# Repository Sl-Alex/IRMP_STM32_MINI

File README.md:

# IRMP Mini Board

This repository contains both PCB and case for IRMP project.
IRMP stands for "**I**nfra**R**ed **M**ulti**P**rotocol decoder".
This board is for STM32 port, which is developed by [Jörg Riechardt][1] and slightly modified (mostly pin assignments) by me.

## Assembly

![Assembly preview][pic_assembly]

## Schematic

![Schematic][pic_schematic]

## Components

As you see, there are not too much components. In fact, the board can be assembled in about half an hour or less, depending on your soldering skills. Please be aware that the smallest components are in size 0402, which is still perfectly solderable, although may require some practice and patience. This is done intentionally to keep the size small.

Here is a list of components to order:

|Reference        | Quantity | Value           | Footprint    | Remark                                                                                  |
| --------------- | -------- | --------------- | ------------ | --------------------------------------------------------------------------------------- |
| C1              | 1        | 100.0µ          | Case B       | Tantalum capacitor                                                                      |
| C2 C5           | 2        | 15p             | 0402         |                                                                                         |
| C3 C6           | 2        | 1.0u            | 0603         |                                                                                         |
| C4 C7 C8 C9 C10 | 5        | 0.1u            | 0402         |                                                                                         |
| D1              | 1        | GREEN           | 0603         |                                                                                         |
| D2              | 1        | RED             | 0603         |                                                                                         |
| R1 R2           | 2        | 20              | 0402         |                                                                                         |
| R3              | 1        | 4k7             | 0402         |                                                                                         |
| R4              | 1        | 100             | 0402         |                                                                                         |
| R5 R6           | 2        | 1k              | 0402         |                                                                                         |
| U1              | 1        | TSOP77338       | Heimdall     | Vishay Heimdall package                                                                 |
| U2              | 1        | MIC5504-3.3YM5  | SOT-23-5     |                                                                                         |
| U3              | 1        | STM32F103T8U6   | VFQFPN-36    |                                                                                         |
| X1              | 1        | 10118192-0001LF | USB2_MICRO_B | Most common USB micro B package. 10118192-0001LF from Amphenol ICC (FCI) fits perfectly |
| XC1             | 1        | 8MHz            | 3225         | 4 pin passive crystal in SMD 3225 package                                               |

## HowTo

- Order all components or make sure they are available
- Order the board. Gerbers are [here][2]
- Solder the board. I'd suggest soldering USB connector and power supply part first, checking if it works and then soldering the rest
- Download DFU bootloader [here][3]
- Flash the DFU bootloader using your favourite SWD adapter. Pin assignments are in the [assembly section](#assembly).
- Connect the board. It will be recognized as "STM32 Bootloader"
- Take the fw [here][4] (the most recent ```*IrmpMini_BL*.bin```)
- Run ```dfu-util -w -D <path_to_the_fw>```. DFU utility can be taken [here][5]
- Wait until the new FW is downloaded
- Reconnect the board

[pic_assembly]: images/pcb.png
[pic_schematic]: images/schematic.png

[1]: https://github.com/j1rie
[2]: https://github.com/Sl-Alex/IRMP_STM32_MINI/tree/main/plots
[3]: https://github.com/Sl-Alex/STM32F103-bootloader/raw/master/binaries/boot.IrmpMini.bin
[4]: https://github.com/Sl-Alex/IRMP_STM32/tree/master/binaries/firmware_for_bootloader
[5]: https://github.com/Sl-Alex/IRMP_STM32/tree/master/binaries/bootloader

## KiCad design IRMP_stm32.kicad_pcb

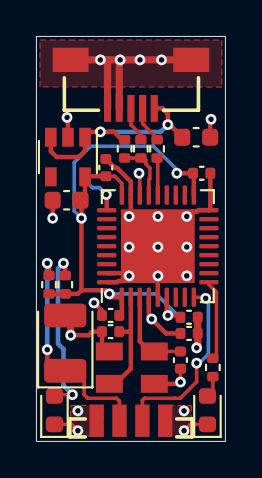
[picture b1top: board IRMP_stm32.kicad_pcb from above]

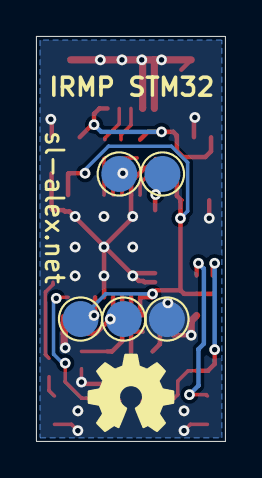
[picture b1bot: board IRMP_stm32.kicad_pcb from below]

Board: 2 copper layers, 10.5 x 22.5 mm, 29 parts (6 on the bottom side), 17 nets.

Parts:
C1: 100.0; CP_EIA-3528-21_Kemet-B
C2, C5: 15p; C_0402_1005Metric
C3, C6: 1.0; C_0603_1608Metric
C4, C7, C8, C9, C10: 0.1; C_0402_1005Metric
D1: GREEN; LED_0603_1608Metric
D2: RED; LED_0603_1608Metric
LG?1: LOGO; OSHW
R1, R2: 20; R_0402_1005Metric
R3: 4k7; R_0402_1005Metric
R4: 100; R_0402_1005Metric
R5, R6: 1k; R_0402_1005Metric
TP1: NRST; TestPoint_Pad_D2.0mm
TP2: 3V3; TestPoint_Pad_D2.0mm
TP3: GND; TestPoint_Pad_D2.0mm
TP4: SWDIO; TestPoint_Pad_D2.0mm
TP5: SWCLK; TestPoint_Pad_D2.0mm
U1: TSOP77338; Vishay_Heimdall
U2: MIC5504-3.3YM5; SOT-23-5
U3: STM32F103T8U6; QFN-36-1EP_6x6mm_P0.5mm_EP4.1x4.1mm
X1: 10118192-0001LF; USB2_MICRO_B_F1
XC1: 8MHz; SMD_3225

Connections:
+3V3: C6.2, C7.2, C8.2, C9.2, C10.2, R4.2, R6.2, TP2.1, U2.5, U3.1, U3.6, U3.19, U3.27
+5V: C3.2, R3.2, U2.1, U2.3, X1.1
/IR_PIN: U1.3, U3.9
/IR_PWR: C1.1, R4.1, U1.2
/LED_PIN: R5.2, U3.10
/NRST: C4.2, TP1.1, U3.4
/OSC_IN: C5.2, U3.2, XC1.3
/OSC_OUT: C2.2, U3.3, XC1.1
/SWCLK: TP5.1, U3.28
/SWDIO: TP4.1, U3.25
/USBCD+: R2.2, X1.3
/USBCD-: R1.2, X1.2
/USBD+: R2.1, R3.1, U3.24
/USBD-: R1.1, U3.23
GNDD: C1.2, C2.1, C3.1, C4.1, C5.1, C6.1, C7.1, C8.1, C9.1, C10.1, D1.1, D2.1, TP3.1, U1.1, U1.4, U2.2, U3.5, U3.18, U3.26, U3.35, U3.36, U3.37, X1.4, X1.5, X1.6, X1.7, XC1.2, XC1.4
unnamed: D1.2, R5.1
unnamed: D2.2, R6.1

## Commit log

2021-01-02 First prototype
2021-01-21 Connect crystal lid to GND
2021-01-22 Set crystal frequency to 8MHz
2021-01-22 Add Gerbers
2021-01-25 Update component values
2021-01-25 Add a README.md
